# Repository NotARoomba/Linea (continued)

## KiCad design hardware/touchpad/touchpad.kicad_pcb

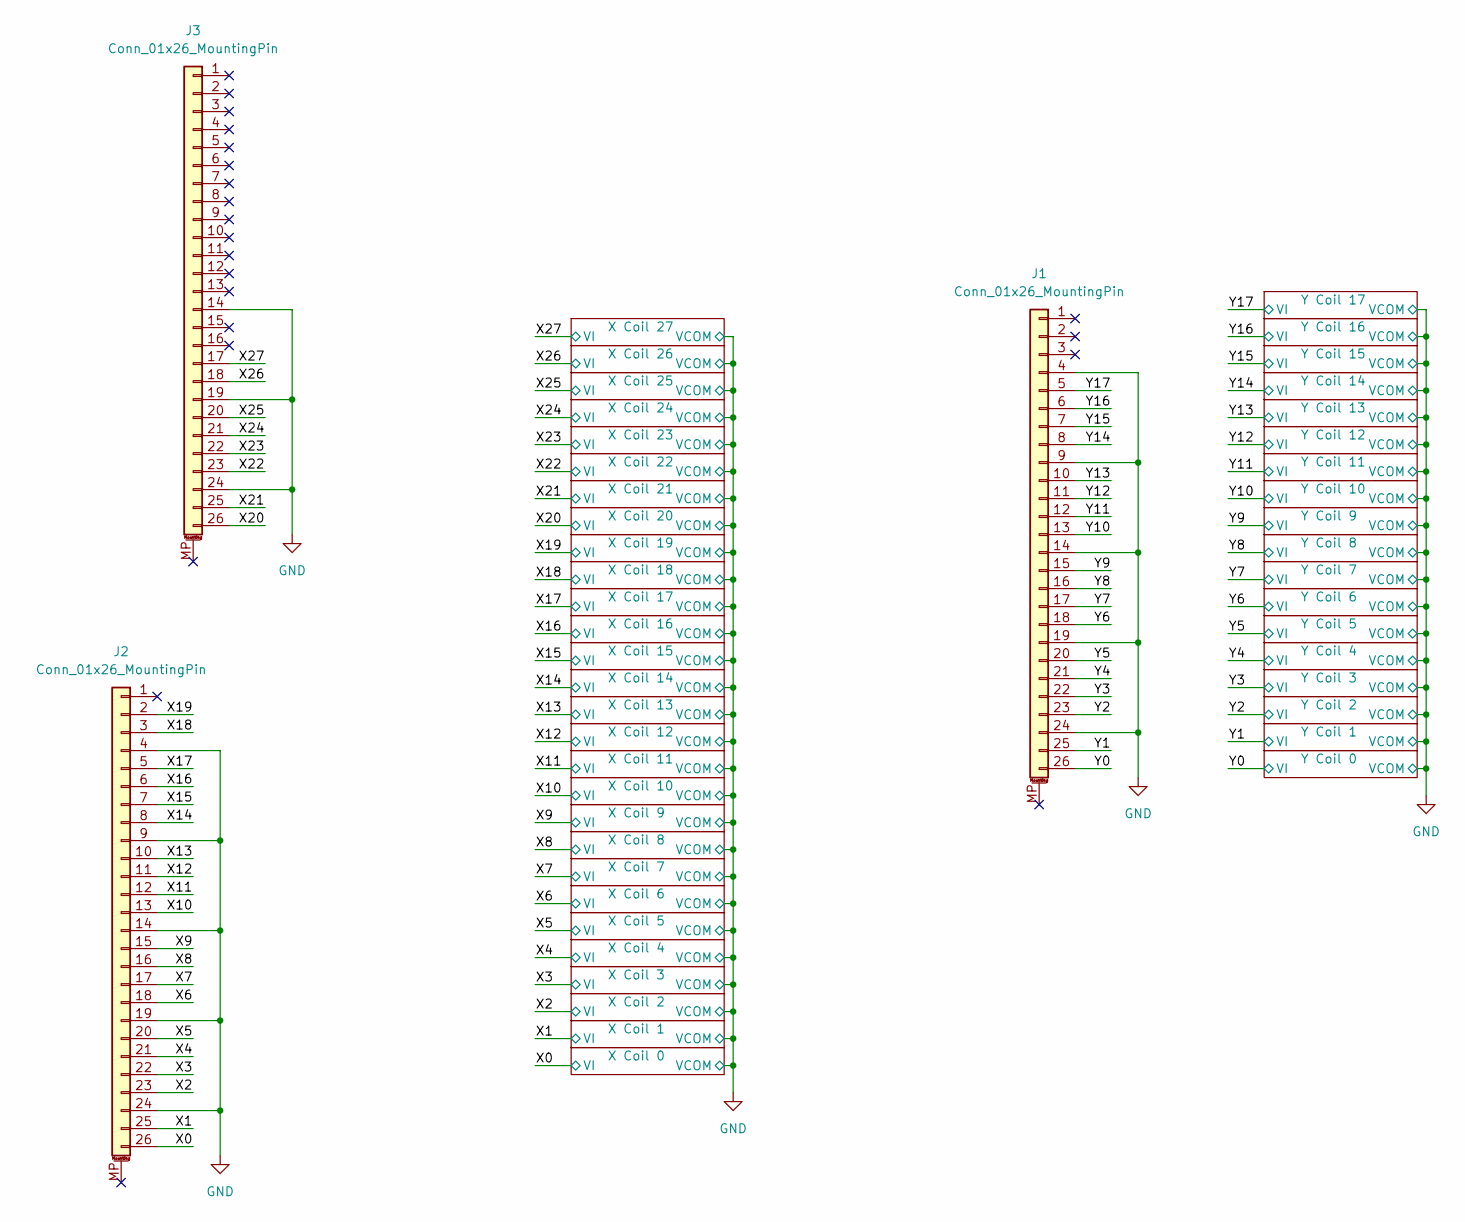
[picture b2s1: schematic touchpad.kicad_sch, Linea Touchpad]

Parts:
J1, J2, J3: Conn_01x26_MountingPin; Hirose_FH12-26S-0.5SH(55)-FPC_1

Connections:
/X0: J2.26; also elsewhere on the board
/X1: J2.25; also elsewhere on the board
/X2: J2.23; also elsewhere on the board
/X3: J2.22; also elsewhere on the board
/X4: J2.21; also elsewhere on the board
/X5: J2.20; also elsewhere on the board
/X6: J2.18; also elsewhere on the board
/X7: J2.17; also elsewhere on the board
/X8: J2.16; also elsewhere on the board
/X9: J2.15; also elsewhere on the board
/X10: J2.13; also elsewhere on the board
/X11: J2.12; also elsewhere on the board
/X12: J2.11; also elsewhere on the board
/X13: J2.10; also elsewhere on the board
/X14: J2.8; also elsewhere on the board
/X15: J2.7; also elsewhere on the board
/X16: J2.6; also elsewhere on the board
/X17: J2.5; also elsewhere on the board
/X18: J2.3; also elsewhere on the board
/X19: J2.2; also elsewhere on the board
/X20: J3.26; also elsewhere on the board
/X21: J3.25; also elsewhere on the board
/X22: J3.23; also elsewhere on the board
/X23: J3.22; also elsewhere on the board
/X24: J3.21; also elsewhere on the board
/X25: J3.20; also elsewhere on the board
/X26: J3.18; also elsewhere on the board
/X27: J3.17; also elsewhere on the board
/Y0: J1.26; also elsewhere on the board
/Y1: J1.25; also elsewhere on the board
/Y2: J1.23; also elsewhere on the board
/Y3: J1.22; also elsewhere on the board
/Y4: J1.21; also elsewhere on the board
/Y5: J1.20; also elsewhere on the board
/Y6: J1.18; also elsewhere on the board
/Y7: J1.17; also elsewhere on the board
/Y8: J1.16; also elsewhere on the board
/Y9: J1.15; also elsewhere on the board
/Y10: J1.13; also elsewhere on the board
/Y11: J1.12; also elsewhere on the board
/Y12: J1.11; also elsewhere on the board
/Y13: J1.10; also elsewhere on the board
/Y14: J1.8; also elsewhere on the board
/Y15: J1.7; also elsewhere on the board
/Y16: J1.6; also elsewhere on the board
/Y17: J1.5; also elsewhere on the board
GND: J1.4, J1.9, J1.14, J1.19, J1.24, J2.4, J2.9, J2.14, J2.19, J2.24, J3.14, J3.19, J3.24; also elsewhere on the board

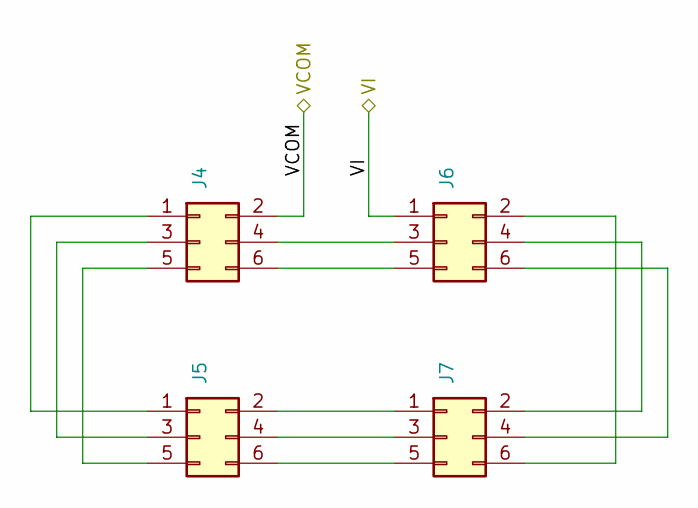
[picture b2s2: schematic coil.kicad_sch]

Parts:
J4, J5, J6, J7: Conn_02x03_Odd_Even; coil_terminal_3p

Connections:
/X0: J6.1; also elsewhere on the board
GND: J4.2; also elsewhere on the board
unnamed: J4.1, J5.1
unnamed: J4.3, J5.3
unnamed: J4.4, J6.3
unnamed: J4.5, J5.5
unnamed: J4.6, J6.5
unnamed: J5.2, J7.1
unnamed: J5.4, J7.3
unnamed: J5.6, J7.5
unnamed: J6.2, J7.6
unnamed: J6.4, J7.2
unnamed: J6.6, J7.4

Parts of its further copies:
J8, J9, J10, J11, J12, J13, J14, J15, J16, J17, J18, J19, J20, J21, J22, J23, J24, J25, J26, J27, J28, J29, J30, J31, J32, J33, J34, J35, J36, J37, J38, J39, J40, J41, J42, J43, J44, J45, J46, J47, J48, J49, J50, J51, J52, J53, J54, J55, J56, J57, J58, J59, J60, J61, J62, J63, J64, J65, J66, J67, J68, J69, J70, J71, J72, J73, J74, J75, J76, J77, J78, J79, J80, J81, J82, J83, J84, J85, J86, J87, J88, J89, J90, J91, J92, J93, J94, J95, J96, J97, J98, J99, J100, J101, J102, J103, J104, J105, J106, J107, J108, J109, J110, J111, J112, J113, J114, J115, J116, J117, J118, J119, J120, J121, J122, J123, J124, J125, J126, J127, J128, J129, J130, J131, J132, J133, J134, J135, J136, J137, J138, J139, J140, J141, J142, J143, J144, J145, J146, J147, J148, J149, J150, J151, J152, J153, J154, J155, J156, J157, J158, J159, J160, J161, J162, J163, J164, J165, J166, J167, J168, J169, J170, J171, J172, J173, J174, J175, J176, J177, J178, J179, J180, J181, J182, J183, J184, J185, J186, J187: Conn_02x03_Odd_Even; coil_terminal_3p

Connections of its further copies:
/X1: J10.1; also elsewhere on the board
/X2: J14.1; also elsewhere on the board
/X3: J18.1; also elsewhere on the board
/X4: J22.1; also elsewhere on the board
/X5: J26.1; also elsewhere on the board
/X6: J30.1; also elsewhere on the board
/X7: J34.1; also elsewhere on the board
/X8: J38.1; also elsewhere on the board
/X9: J42.1; also elsewhere on the board
/X10: J46.1; also elsewhere on the board
/X11: J186.1; also elsewhere on the board
/X12: J50.1; also elsewhere on the board
/X13: J54.1; also elsewhere on the board
/X14: J58.1; also elsewhere on the board
/X15: J62.1; also elsewhere on the board
/X16: J66.1; also elsewhere on the board
/X17: J70.1; also elsewhere on the board
/X18: J74.1; also elsewhere on the board
/X19: J78.1; also elsewhere on the board
/X20: J82.1; also elsewhere on the board
/X21: J86.1; also elsewhere on the board
/X22: J90.1; also elsewhere on the board
/X23: J94.1; also elsewhere on the board
/X24: J98.1; also elsewhere on the board
/X25: J102.1; also elsewhere on the board
/X26: J106.1; also elsewhere on the board
/X27: J110.1; also elsewhere on the board
/Y0: J114.1; also elsewhere on the board
/Y1: J118.1; also elsewhere on the board
/Y2: J122.1; also elsewhere on the board
/Y3: J126.1; also elsewhere on the board
/Y4: J130.1; also elsewhere on the board
/Y5: J134.1; also elsewhere on the board
/Y6: J138.1; also elsewhere on the board
/Y7: J142.1; also elsewhere on the board
/Y8: J146.1; also elsewhere on the board
/Y9: J150.1; also elsewhere on the board
/Y10: J154.1; also elsewhere on the board
/Y11: J158.1; also elsewhere on the board
/Y12: J162.1; also elsewhere on the board
/Y13: J166.1; also elsewhere on the board
/Y14: J170.1; also elsewhere on the board
/Y15: J174.1; also elsewhere on the board
/Y16: J178.1; also elsewhere on the board
/Y17: J182.1; also elsewhere on the board
GND: J8.2, J12.2, J16.2, J20.2, J24.2, J28.2, J32.2, J36.2, J40.2, J44.2, J48.2, J52.2, J56.2, J60.2, J64.2, J68.2, J72.2, J76.2, J80.2, J84.2, J88.2, J92.2, J96.2, J100.2, J104.2, J108.2, J112.2, J116.2, J120.2, J124.2, J128.2, J132.2, J136.2, J140.2, J144.2, J148.2, J152.2, J156.2, J160.2, J164.2, J168.2, J172.2, J176.2, J180.2, J184.2; also elsewhere on the board
unnamed: J8.1, J9.1
unnamed: J8.3, J9.3
unnamed: J8.5, J9.5
unnamed: J10.2, J11.6
unnamed: J8.4, J10.3
unnamed: J10.4, J11.2
unnamed: J8.6, J10.5
unnamed: J10.6, J11.4
unnamed: J9.2, J11.1
unnamed: J9.4, J11.3
unnamed: J9.6, J11.5
unnamed: J12.1, J13.1
unnamed: J12.3, J13.3
unnamed: J12.4, J14.3
unnamed: J12.5, J13.5
unnamed: J12.6, J14.5
unnamed: J13.2, J15.1
unnamed: J13.4, J15.3
unnamed: J13.6, J15.5
unnamed: J14.2, J15.6
unnamed: J14.4, J15.2
unnamed: J14.6, J15.4
unnamed: J16.1, J17.1
unnamed: J16.3, J17.3
unnamed: J16.4, J18.3
unnamed: J16.5, J17.5
unnamed: J16.6, J18.5
unnamed: J17.2, J19.1
unnamed: J17.4, J19.3
unnamed: J17.6, J19.5
unnamed: J18.2, J19.6
unnamed: J18.4, J19.2
unnamed: J18.6, J19.4
unnamed: J20.1, J21.1
unnamed: J20.3, J21.3
unnamed: J20.4, J22.3
unnamed: J20.5, J21.5
unnamed: J20.6, J22.5
unnamed: J21.2, J23.1
unnamed: J21.4, J23.3
unnamed: J21.6, J23.5
unnamed: J22.2, J23.6
unnamed: J22.4, J23.2
unnamed: J22.6, J23.4
unnamed: J24.1, J25.1
unnamed: J24.3, J25.3
unnamed: J24.4, J26.3
unnamed: J24.5, J25.5
unnamed: J24.6, J26.5
unnamed: J25.2, J27.1
unnamed: J25.4, J27.3
unnamed: J25.6, J27.5
unnamed: J26.2, J27.6
unnamed: J26.4, J27.2
unnamed: J26.6, J27.4
unnamed: J28.1, J29.1
unnamed: J28.3, J29.3
unnamed: J28.4, J30.3
unnamed: J28.5, J29.5
unnamed: J28.6, J30.5
unnamed: J29.2, J31.1
unnamed: J29.4, J31.3
unnamed: J29.6, J31.5
unnamed: J30.2, J31.6
unnamed: J30.4, J31.2
unnamed: J30.6, J31.4
unnamed: J32.1, J33.1
unnamed: J32.3, J33.3
unnamed: J32.4, J34.3
unnamed: J32.5, J33.5
unnamed: J32.6, J34.5
unnamed: J33.2, J35.1
unnamed: J33.4, J35.3
unnamed: J33.6, J35.5
unnamed: J34.2, J35.6
unnamed: J34.4, J35.2
unnamed: J34.6, J35.4
unnamed: J36.1, J37.1
unnamed: J36.3, J37.3
unnamed: J36.4, J38.3
unnamed: J36.5, J37.5
unnamed: J36.6, J38.5
unnamed: J37.2, J39.1
unnamed: J37.4, J39.3
unnamed: J37.6, J39.5
unnamed: J38.2, J39.6
unnamed: J38.4, J39.2
unnamed: J38.6, J39.4
unnamed: J40.1, J41.1
unnamed: J40.3, J41.3
unnamed: J40.4, J42.3
unnamed: J40.5, J41.5
unnamed: J40.6, J42.5
unnamed: J41.2, J43.1
unnamed: J41.4, J43.3
unnamed: J41.6, J43.5
unnamed: J42.2, J43.6
unnamed: J42.4, J43.2
unnamed: J42.6, J43.4
unnamed: J44.1, J45.1
unnamed: J44.3, J45.3
unnamed: J44.4, J46.3
unnamed: J44.5, J45.5
unnamed: J44.6, J46.5
unnamed: J45.2, J47.1
unnamed: J45.4, J47.3
unnamed: J45.6, J47.5
unnamed: J46.2, J47.6
unnamed: J46.4, J47.2
unnamed: J46.6, J47.4
unnamed: J48.1, J49.1
unnamed: J48.3, J49.3
unnamed: J48.4, J50.3
unnamed: J48.5, J49.5
unnamed: J48.6, J50.5
unnamed: J49.2, J51.1
unnamed: J49.4, J51.3
unnamed: J49.6, J51.5
unnamed: J50.2, J51.6
unnamed: J50.4, J51.2
unnamed: J50.6, J51.4
unnamed: J52.1, J53.1
unnamed: J52.3, J53.3
unnamed: J52.4, J54.3
unnamed: J52.5, J53.5
unnamed: J52.6, J54.5
unnamed: J53.2, J55.1
unnamed: J53.4, J55.3
unnamed: J53.6, J55.5
unnamed: J54.2, J55.6
unnamed: J54.4, J55.2
unnamed: J54.6, J55.4
unnamed: J56.1, J57.1
unnamed: J56.3, J57.3
unnamed: J56.4, J58.3
unnamed: J56.5, J57.5
unnamed: J56.6, J58.5
unnamed: J57.2, J59.1
unnamed: J57.4, J59.3
unnamed: J57.6, J59.5
unnamed: J58.2, J59.6
unnamed: J58.4, J59.2
unnamed: J58.6, J59.4
unnamed: J60.1, J61.1
unnamed: J60.3, J61.3
unnamed: J60.4, J62.3
unnamed: J60.5, J61.5
unnamed: J60.6, J62.5
unnamed: J61.2, J63.1
unnamed: J61.4, J63.3
unnamed: J61.6, J63.5
unnamed: J62.2, J63.6
unnamed: J62.4, J63.2
unnamed: J62.6, J63.4
unnamed: J64.1, J65.1
unnamed: J64.3, J65.3
unnamed: J64.4, J66.3
unnamed: J64.5, J65.5
unnamed: J64.6, J66.5
unnamed: J65.2, J67.1
unnamed: J65.4, J67.3
unnamed: J65.6, J67.5
unnamed: J66.2, J67.6
unnamed: J66.4, J67.2
unnamed: J66.6, J67.4
unnamed: J68.1, J69.1
unnamed: J68.3, J69.3
unnamed: J68.4, J70.3
unnamed: J68.5, J69.5
unnamed: J68.6, J70.5
unnamed: J69.2, J71.1
unnamed: J69.4, J71.3
unnamed: J69.6, J71.5
unnamed: J70.2, J71.6
unnamed: J70.4, J71.2
unnamed: J70.6, J71.4
unnamed: J72.1, J73.1
unnamed: J72.3, J73.3
unnamed: J72.4, J74.3
unnamed: J72.5, J73.5
unnamed: J72.6, J74.5
unnamed: J73.2, J75.1
unnamed: J73.4, J75.3
unnamed: J73.6, J75.5
unnamed: J74.2, J75.6
unnamed: J74.4, J75.2
unnamed: J74.6, J75.4
unnamed: J76.1, J77.1
unnamed: J76.3, J77.3
unnamed: J76.4, J78.3
unnamed: J76.5, J77.5
unnamed: J76.6, J78.5
unnamed: J77.2, J79.1
unnamed: J77.4, J79.3
unnamed: J77.6, J79.5
unnamed: J78.2, J79.6
unnamed: J78.4, J79.2
unnamed: J78.6, J79.4
unnamed: J80.1, J81.1
unnamed: J80.3, J81.3
unnamed: J80.4, J82.3
unnamed: J80.5, J81.5
unnamed: J80.6, J82.5
unnamed: J81.2, J83.1
unnamed: J81.4, J83.3
unnamed: J81.6, J83.5
unnamed: J82.2, J83.6
unnamed: J82.4, J83.2
unnamed: J82.6, J83.4
unnamed: J84.1, J85.1
unnamed: J84.3, J85.3
unnamed: J84.4, J86.3
unnamed: J84.5, J85.5
unnamed: J84.6, J86.5
unnamed: J85.2, J87.1
unnamed: J85.4, J87.3
unnamed: J85.6, J87.5
unnamed: J86.2, J87.6
unnamed: J86.4, J87.2
unnamed: J86.6, J87.4
unnamed: J88.1, J89.1
unnamed: J88.3, J89.3
unnamed: J88.4, J90.3
unnamed: J88.5, J89.5
unnamed: J88.6, J90.5
unnamed: J89.2, J91.1
unnamed: J89.4, J91.3
unnamed: J89.6, J91.5
unnamed: J90.2, J91.6
unnamed: J90.4, J91.2
unnamed: J90.6, J91.4
unnamed: J92.1, J93.1
unnamed: J92.3, J93.3
unnamed: J92.4, J94.3
unnamed: J92.5, J93.5
unnamed: J92.6, J94.5
unnamed: J93.2, J95.1
unnamed: J93.4, J95.3
unnamed: J93.6, J95.5
unnamed: J94.2, J95.6
unnamed: J94.4, J95.2
unnamed: J94.6, J95.4
unnamed: J96.1, J97.1
unnamed: J96.3, J97.3
unnamed: J96.4, J98.3
unnamed: J96.5, J97.5
unnamed: J96.6, J98.5
unnamed: J97.2, J99.1
unnamed: J97.4, J99.3
unnamed: J97.6, J99.5
unnamed: J98.2, J99.6
unnamed: J98.4, J99.2
unnamed: J98.6, J99.4
unnamed: J100.1, J101.1
unnamed: J100.3, J101.3
unnamed: J100.4, J102.3
unnamed: J100.5, J101.5
unnamed: J100.6, J102.5
unnamed: J101.2, J103.1
unnamed: J101.4, J103.3
unnamed: J101.6, J103.5
unnamed: J102.2, J103.6
unnamed: J102.4, J103.2
unnamed: J102.6, J103.4
unnamed: J104.1, J105.1
unnamed: J104.3, J105.3
unnamed: J104.4, J106.3
unnamed: J104.5, J105.5
unnamed: J104.6, J106.5
unnamed: J105.2, J107.1
unnamed: J105.4, J107.3
unnamed: J105.6, J107.5
unnamed: J106.2, J107.6
unnamed: J106.4, J107.2
unnamed: J106.6, J107.4
unnamed: J108.1, J109.1
unnamed: J108.3, J109.3
unnamed: J108.4, J110.3
unnamed: J108.5, J109.5
unnamed: J108.6, J110.5
unnamed: J109.2, J111.1
unnamed: J109.4, J111.3
unnamed: J109.6, J111.5
unnamed: J110.2, J111.6
unnamed: J110.4, J111.2
unnamed: J110.6, J111.4
unnamed: J112.1, J113.1
unnamed: J112.3, J113.3
unnamed: J112.4, J114.3
unnamed: J112.5, J113.5
unnamed: J112.6, J114.5
unnamed: J113.2, J115.1
unnamed: J113.4, J115.3
unnamed: J113.6, J115.5
unnamed: J114.2, J115.6
unnamed: J114.4, J115.2
unnamed: J114.6, J115.4
unnamed: J116.1, J117.1
unnamed: J116.3, J117.3
unnamed: J116.4, J118.3
unnamed: J116.5, J117.5
unnamed: J116.6, J118.5
unnamed: J117.2, J119.1
unnamed: J117.4, J119.3
unnamed: J117.6, J119.5
unnamed: J118.2, J119.6
unnamed: J118.4, J119.2
unnamed: J118.6, J119.4
unnamed: J120.1, J121.1
unnamed: J120.3, J121.3
unnamed: J120.4, J122.3
unnamed: J120.5, J121.5
unnamed: J120.6, J122.5
unnamed: J121.2, J123.1
unnamed: J121.4, J123.3
unnamed: J121.6, J123.5
unnamed: J122.2, J123.6
unnamed: J122.4, J123.2
unnamed: J122.6, J123.4
unnamed: J124.1, J125.1
unnamed: J124.3, J125.3
unnamed: J124.4, J126.3
unnamed: J124.5, J125.5
unnamed: J124.6, J126.5
unnamed: J125.2, J127.1
unnamed: J125.4, J127.3
unnamed: J125.6, J127.5
unnamed: J126.2, J127.6
unnamed: J126.4, J127.2
unnamed: J126.6, J127.4
unnamed: J128.1, J129.1
unnamed: J128.3, J129.3
unnamed: J128.4, J130.3
unnamed: J128.5, J129.5
unnamed: J128.6, J130.5
unnamed: J129.2, J131.1
unnamed: J129.4, J131.3
unnamed: J129.6, J131.5
unnamed: J130.2, J131.6
unnamed: J130.4, J131.2
unnamed: J130.6, J131.4
unnamed: J132.1, J133.1
unnamed: J132.3, J133.3
unnamed: J132.4, J134.3
unnamed: J132.5, J133.5
unnamed: J132.6, J134.5
unnamed: J133.2, J135.1
unnamed: J133.4, J135.3
unnamed: J133.6, J135.5
unnamed: J134.2, J135.6
unnamed: J134.4, J135.2
unnamed: J134.6, J135.4
unnamed: J136.1, J137.1
unnamed: J136.3, J137.3
unnamed: J136.4, J138.3
unnamed: J136.5, J137.5
unnamed: J136.6, J138.5
unnamed: J137.2, J139.1
unnamed: J137.4, J139.3
unnamed: J137.6, J139.5
unnamed: J138.2, J139.6
unnamed: J138.4, J139.2
unnamed: J138.6, J139.4
unnamed: J140.1, J141.1
unnamed: J140.3, J141.3
unnamed: J140.4, J142.3
unnamed: J140.5, J141.5
unnamed: J140.6, J142.5
unnamed: J141.2, J143.1
unnamed: J141.4, J143.3
unnamed: J141.6, J143.5
unnamed: J142.2, J143.6
unnamed: J142.4, J143.2
unnamed: J142.6, J143.4
unnamed: J144.1, J145.1
unnamed: J144.3, J145.3
unnamed: J144.4, J146.3
unnamed: J144.5, J145.5
unnamed: J144.6, J146.5
unnamed: J145.2, J147.1
unnamed: J145.4, J147.3
unnamed: J145.6, J147.5
unnamed: J146.2, J147.6
unnamed: J146.4, J147.2
unnamed: J146.6, J147.4
unnamed: J148.1, J149.1
unnamed: J148.3, J149.3
unnamed: J148.4, J150.3
unnamed: J148.5, J149.5
unnamed: J148.6, J150.5
unnamed: J149.2, J151.1
unnamed: J149.4, J151.3
unnamed: J149.6, J151.5
unnamed: J150.2, J151.6
unnamed: J150.4, J151.2
unnamed: J150.6, J151.4
unnamed: J152.1, J153.1
unnamed: J152.3, J153.3
unnamed: J152.4, J154.3
unnamed: J152.5, J153.5
unnamed: J152.6, J154.5
unnamed: J153.2, J155.1
unnamed: J153.4, J155.3
unnamed: J153.6, J155.5
unnamed: J154.2, J155.6
unnamed: J154.4, J155.2
unnamed: J154.6, J155.4
unnamed: J156.1, J157.1
unnamed: J156.3, J157.3
unnamed: J156.4, J158.3
unnamed: J156.5, J157.5
unnamed: J156.6, J158.5
unnamed: J157.2, J159.1
unnamed: J157.4, J159.3
unnamed: J157.6, J159.5
unnamed: J158.2, J159.6
unnamed: J158.4, J159.2
unnamed: J158.6, J159.4
unnamed: J160.1, J161.1
unnamed: J160.3, J161.3
unnamed: J160.4, J162.3
unnamed: J160.5, J161.5
unnamed: J160.6, J162.5
unnamed: J161.2, J163.1
unnamed: J161.4, J163.3
unnamed: J161.6, J163.5
unnamed: J162.2, J163.6
unnamed: J162.4, J163.2
unnamed: J162.6, J163.4
unnamed: J164.1, J165.1
unnamed: J164.3, J165.3
unnamed: J164.4, J166.3
unnamed: J164.5, J165.5
unnamed: J164.6, J166.5
unnamed: J165.2, J167.1
unnamed: J165.4, J167.3
unnamed: J165.6, J167.5
unnamed: J166.2, J167.6
unnamed: J166.4, J167.2
unnamed: J166.6, J167.4
unnamed: J168.1, J169.1
unnamed: J168.3, J169.3
unnamed: J168.4, J170.3
unnamed: J168.5, J169.5
unnamed: J168.6, J170.5
unnamed: J169.2, J171.1
unnamed: J169.4, J171.3
unnamed: J169.6, J171.5
unnamed: J170.2, J171.6
unnamed: J170.4, J171.2
unnamed: J170.6, J171.4
unnamed: J172.1, J173.1
unnamed: J172.3, J173.3
unnamed: J172.4, J174.3
unnamed: J172.5, J173.5
unnamed: J172.6, J174.5
unnamed: J173.2, J175.1
unnamed: J173.4, J175.3
unnamed: J173.6, J175.5
unnamed: J174.2, J175.6
unnamed: J174.4, J175.2
unnamed: J174.6, J175.4
unnamed: J176.1, J177.1
unnamed: J176.3, J177.3
unnamed: J176.4, J178.3
unnamed: J176.5, J177.5
unnamed: J176.6, J178.5
unnamed: J177.2, J179.1
unnamed: J177.4, J179.3
unnamed: J177.6, J179.5
unnamed: J178.2, J179.6
unnamed: J178.4, J179.2
unnamed: J178.6, J179.4
unnamed: J180.1, J181.1
unnamed: J180.3, J181.3
unnamed: J180.4, J182.3
unnamed: J180.5, J181.5
unnamed: J180.6, J182.5
unnamed: J181.2, J183.1
unnamed: J181.4, J183.3
unnamed: J181.6, J183.5
unnamed: J182.2, J183.6
unnamed: J182.4, J183.2
unnamed: J182.6, J183.4
unnamed: J184.1, J185.1
unnamed: J184.3, J185.3
unnamed: J184.4, J186.3
unnamed: J184.5, J185.5
unnamed: J184.6, J186.5
unnamed: J185.2, J187.1
unnamed: J185.4, J187.3
unnamed: J185.6, J187.5
unnamed: J186.2, J187.6
unnamed: J186.4, J187.2
unnamed: J186.6, J187.4

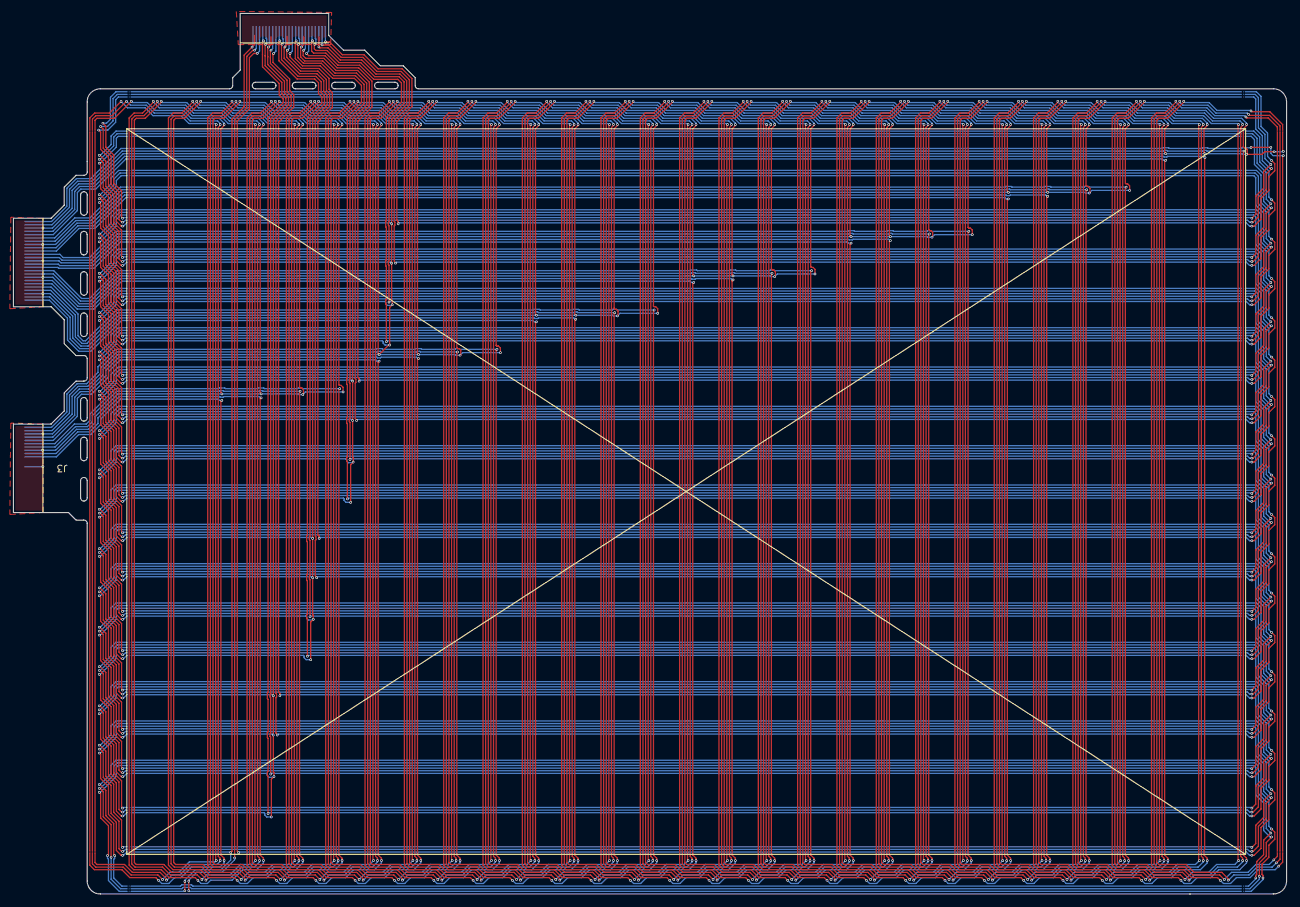
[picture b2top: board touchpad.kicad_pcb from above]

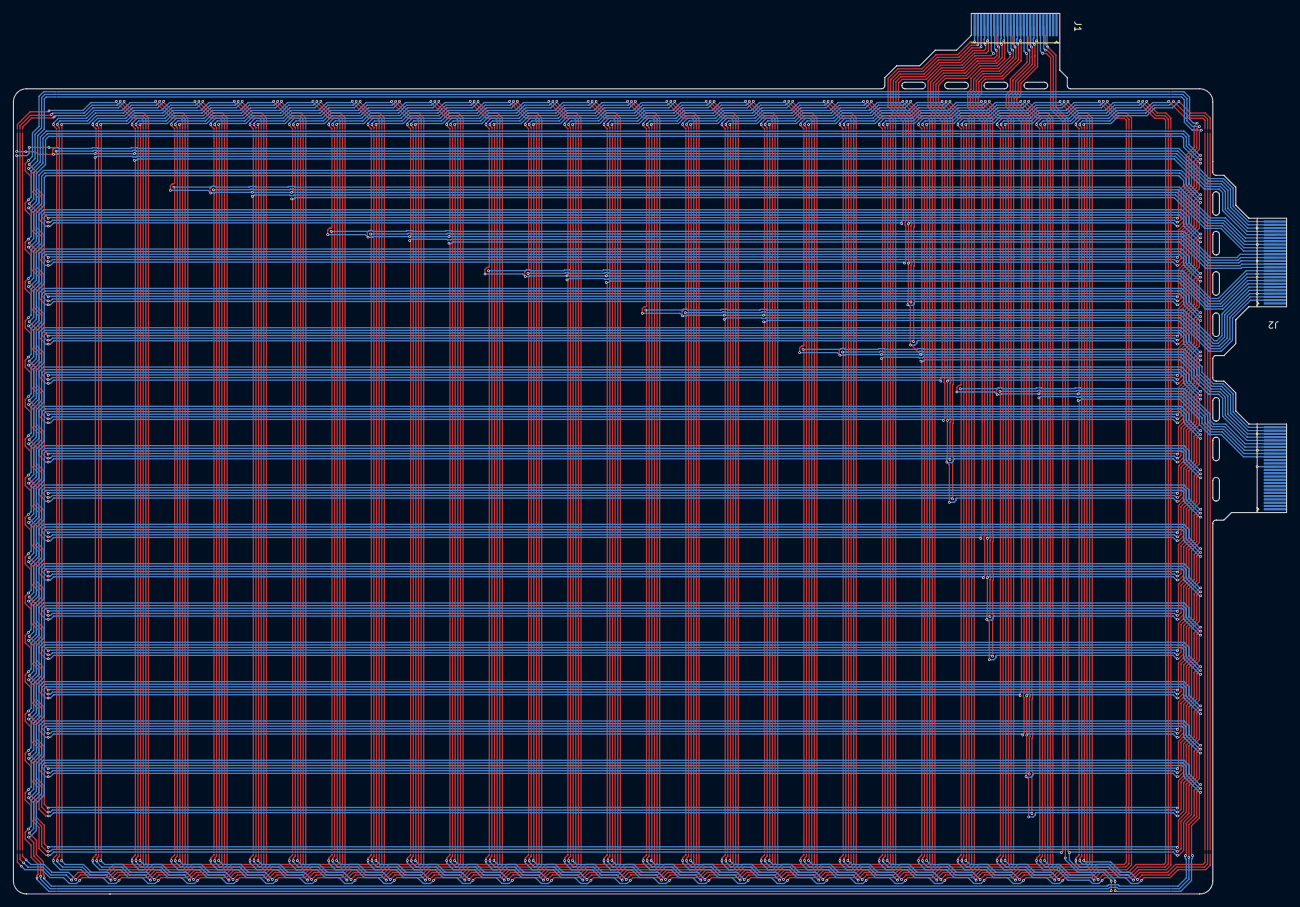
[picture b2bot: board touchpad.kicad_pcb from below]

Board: 2 copper layers, 194.2 x 134.4 mm, 187 parts (75 on the bottom side), 553 nets.

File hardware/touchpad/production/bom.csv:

Designator,Footprint,Quantity,Value,LCSC Part #
"J1, J2, J3",Hirose_FH12-26S-0.5SH(55)-FPC_1,3,Conn_01x26_MountingPin,
"J10, J100, J101, J102, J103, J104, J105, J106, J107, J108, J109, J11, J110, J111, J112, J113, J114, J115, J116, J117, J118, J119, J12, J120, J121, J122, J123, J124, J125, J126, J127, J128, J129, J13, J130, J131, J132, J133, J134, J135, J136, J137, J138, J139, J14, J140, J141, J142, J143, J144, J145, J146, J147, J148, J149, J15, J150, J151, J152, J153, J154, J155, J156, J157, J158, J159, J16, J160, J161, J162, J163, J164, J165, J166, J167, J168, J169, J17, J170, J171, J172, J173, J174, J175, J176, J177, J178, J179, J18, J180, J181, J182, J183, J184, J185, J186, J187, J19, J20, J21, J22, J23, J24, J25, J26, J27, J28, J29, J30, J31, J32, J33, J34, J35, J36, J37, J38, J39, J4, J40, J41, J42, J43, J44, J45, J46, J47, J48, J49, J5, J50, J51, J52, J53, J54, J55, J56, J57, J58, J59, J6, J60, J61, J62, J63, J64, J65, J66, J67, J68, J69, J7, J70, J71, J72, J73, J74, J75, J76, J77, J78, J79, J8, J80, J81, J82, J83, J84, J85, J86, J87, J88, J89, J9, J90, J91, J92, J93, J94, J95, J96, J97, J98, J99",coil_terminal_3p,184,Conn_02x03_Odd_Even,

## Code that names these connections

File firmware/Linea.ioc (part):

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Mcu.Name=STM32WB55RGVx
Mcu.Package=VFQFPN68
Mcu.UserName=STM32WB55RGVx
PA0.GPIOParameters=GPIO_Label
PA0.GPIO_Label=DISCHARGE
PA0.Signal=GPIO_Output
PA1.Signal=S_TIM2_CH2
PA10.GPIOParameters=GPIO_Speed
PA10.GPIO_Speed=GPIO_SPEED_FREQ_MEDIUM
PA10.Signal=S_TIM1_CH3
PA11.Mode=Device
PA11.Signal=USB_DM
PA12.Mode=Device
PA12.Signal=USB_DP
PA14.GPIOParameters=GPIO_Label
PA14.GPIO_Label=S2
PA14.Signal=GPIO_Output
PA15.GPIOParameters=GPIO_Label
PA15.GPIO_Label=S1
PA15.Signal=GPIO_Output
PA2.Signal=S_TIM2_CH3
PA7.GPIOParameters=GPIO_Speed
PA7.GPIO_Speed=GPIO_SPEED_FREQ_MEDIUM
PA7.Mode=PWM Generation1 CH1 CH1N
PA7.Signal=TIM1_CH1N
PA8.GPIOParameters=GPIO_Speed
PA8.GPIO_Speed=GPIO_SPEED_FREQ_MEDIUM
PA8.Signal=S_TIM1_CH1
PA9.Mode=Asynchronous
PA9.Signal=USART1_TX
PB15.GPIOParameters=GPIO_Speed
PB15.GPIO_Speed=GPIO_SPEED_FREQ_MEDIUM
PB15.Mode=PWM Generation3 CH3 CH3N
PB15.Signal=TIM1_CH3N
PB3.GPIOParameters=GPIO_Label
PB3.GPIO_Label=E2N
PB3.Signal=GPIO_Output
PB4.GPIOParameters=GPIO_Label
PB4.GPIO_Label=E1N
PB4.Signal=GPIO_Output
PB5.GPIOParameters=GPIO_Label
PB5.GPIO_Label=E0N
PB5.Signal=GPIO_Output
PB6.GPIOParameters=GPIO_Speed,GPIO_Label
PB6.GPIO_Label=EXCITER
PB6.GPIO_Speed=GPIO_SPEED_FREQ_VERY_HIGH
PB6.Mode=PWM Generation1 CH1N
PB6.Signal=TIM16_CH1N
PB7.Mode=Asynchronous
PB7.Signal=USART1_RX
PB8.Mode=I2C
PB8.Signal=I2C1_SCL
PB9.Mode=I2C
PB9.Signal=I2C1_SDA
PC10.GPIOParameters=GPIO_Label
PC10.GPIO_Label=S0
PC10.Signal=GPIO_Output
PC12.GPIOParameters=GPIO_Label
PC12.GPIO_Label=E5N
PC12.Signal=GPIO_Output
PC13.Signal=GPIO_Input
PC14-OSC32_IN.Mode=LSE-External-Oscillator
PC14-OSC32_IN.Signal=RCC_OSC32_IN
PC15-OSC32_OUT.Mode=LSE-External-Oscillator
PC15-OSC32_OUT.Signal=RCC_OSC32_OUT
PC2.Signal=ADCx_IN3
PD0.GPIOParameters=GPIO_Label
PD0.GPIO_Label=E4N
PD0.Signal=GPIO_Output
PD1.GPIOParameters=GPIO_Label
PD1.GPIO_Label=E3N
PD1.Signal=GPIO_Output
PH3-BOOT0.Signal=GPIO_Input
RCC.HSE_VALUE=32000000
RCC.SYSCLKFreq_VALUE=64000000
RCC.SYSCLKSource=RCC_SYSCLKSOURCE_PLLCLK
board=custom

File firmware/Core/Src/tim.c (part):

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    __HAL_RCC_GPIOA_CLK_ENABLE();
    __HAL_RCC_GPIOB_CLK_ENABLE();
    /**TIM1 GPIO Configuration
    PA7     ------> TIM1_CH1N
    PA8     ------> TIM1_CH1
    PB15     ------> TIM1_CH3N
    PA10     ------> TIM1_CH3
    */
    GPIO_InitStruct.Pin = GPIO_PIN_7|GPIO_PIN_8|GPIO_PIN_10;
    GPIO_InitStruct.Mode = GPIO_MODE_AF_PP;
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
    __HAL_RCC_GPIOB_CLK_ENABLE();
    /**TIM16 GPIO Configuration
    PB6     ------> TIM16_CH1N
    */
    GPIO_InitStruct.Pin = EXCITER_Pin;
    GPIO_InitStruct.Mode = GPIO_MODE_AF_PP;
    GPIO_InitStruct.Pull = GPIO_NOPULL;
    GPIO_InitStruct.Speed = GPIO_SPEED_FREQ_VERY_HIGH;
    GPIO_InitStruct.Alternate = GPIO_AF14_TIM16;
    HAL_GPIO_Init(EXCITER_GPIO_Port, &GPIO_InitStruct);

  /* USER CODE BEGIN TIM16_MspPostInit 1 */

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
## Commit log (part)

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2025-06-29 added stuff
2025-06-30 finished touchpad
2025-06-30 started on board
2025-07-01 started schematics
2025-07-01 update schmatic
2025-07-02 fixed stuff
2025-07-02 added .2mm spacing
2025-07-03 update footprints
2025-07-03 stuff
2025-07-04 added more stuff
2025-07-04 fnished shcamtic
2025-07-04 aaaaa
2025-07-05 added touches
2025-07-06 pcb power start
2025-07-13 bunch o f stuff
2025-07-13 locks
2025-07-13 finished board
2025-07-13 whoops
2025-07-13 references and credits
2025-07-13 update hours based on screen time
2025-07-13 battery adn 3d stuff
2025-07-15 impdance matching
2025-07-16 esd prtot
2025-07-21 gerbers
2025-08-15 add stff
2025-08-15 bl stuff
2025-08-16 add cdc
2025-08-16 another usb lib
2025-08-16 its building
2025-08-16 added include
2025-08-16 nesscary fils
2025-08-17 code
2025-09-09 before big change
2025-10-03 stuff
    stuff
2025-11-18 layer
